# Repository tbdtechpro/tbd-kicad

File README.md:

# tbd-kicad

KiCad 9 symbols, footprints and 3D models for hobby-electronics modules that are awkward to find ready-made:
development boards, display modules, audio DACs, level-shifter breakouts, an encoder module, optocouplers, solderable
breadboard and proto boards, a 3.5 mm jack and a MIDI shield. Each part is complete: a symbol with sensible pin types, a footprint
with the real hole pattern, a 3D body for the viewer, and a note on where every dimension came from.

Everything here is generated from Python scripts, so a measurement fix rebuilds the whole library consistently. Use
it under CC-BY-SA 4.0 with the KiCad library exception: designs made with it are yours, no attribution needed on boards.

## Parts

| Part | Symbol | Footprint | 3D | Geometry source |
|---|---|---|---|---|
| **Development boards** | | | | |
| PJRC Teensy 4.1 | `Teensy_4.1` | `Teensy41` | STEP + coloured VRML | XenGi library (exact) |
| Espressif ESP32-S3-DevKitC-1 (and N16R8 clones) | `ESP32-S3-DevKitC-1` | `ESP32-S3-DevKitC-1` | VRML + STEP | Espressif library (exact) |
| DFRobot Beetle RP2350 (DFR1188) | `Beetle_RP2350_DFR1188` | `Beetle_RP2350_DFR1188_THT`, `_SMD` | VRML + STEP (THT) | DFRobot CAD (exact) |
| Waveshare RP2040-Zero form factor | `RP2040-Zero` | `RP2040-Zero` | VRML + STEP | Waveshare drawing (edge pins exact, back pads approx.) |
| Waveshare RP2350B-Plus-W (Pico 2 W form factor, RP2350B) | `RP2350B-Plus-W` | `RP2350B-Plus-W` | VRML + STEP | Waveshare drawing + board (pins exact, back pads +/-0.3 mm) |
| **Displays** | | | | |
| 2.8" ILI9341 SPI TFT, 14-pin (lcdwiki MSP2806/MSP2807) | `TFT_2.8in_ILI9341_SPI_MSP2806` | same | VRML + STEP | lcdwiki drawing (exact) |
| 1.5" SH1107 128x128 OLED, I2C 4-pin (HiLetgo / GME128128-01-IIC) | `OLED_1.5in_SH1107_128x128_I2C` | same | VRML + STEP | calipers (PCB, holes, header, glass) |
| 1.28" round GC9A01 IPS, 7-pin | `GC9A01_Round_1.28in_7pin` | same | VRML + STEP | header exact, outline from photos |
| **Audio** | | | | |
| Adafruit PCM5102 / PCM5100 I2S DAC (6250 / 6251) | `Adafruit_PCM510x_I2S_DAC` | same | VRML + STEP | Adafruit EagleCAD (exact) |
| Lonely Binary TK103 PCM5102A I2S DAC (right-angle header) | `TK103_PCM5102A_I2S_DAC` | `TK103_Module_RA_Header` | vendor STEP, see note | vendor STEP (exact) |
| Kycon STX-3120-3B 3.5 mm stereo jack (Adafruit 1699) | `AudioJack_3.5mm_STX-3120-3B` | `Jack_3.5mm_Kycon_STX-3120-3B_Horizontal` | VRML + STEP | Kycon drawing (exact) |
| Arduino UNO MIDI shield (3x DIN-5, 6N138, marking K194725ASJH) | `MIDI_Shield_DIN5x3_6N138` | `MIDI_Shield_K194725ASJH` | VRML + STEP (from `projects/midi-shield`) | UNO 6+6/8+8 header pattern (exact), parts from photos and calipers |
| **Breakouts and modules** | | | | |
| Adafruit TXB0104 bi-directional level shifter (1875) | `Adafruit_TXB0104_Level_Shifter` | `Adafruit_TXB0104_Breakout` | VRML + STEP | Adafruit EagleCAD (exact) |
| Adafruit BSS138 4-channel I2C-safe level shifter (757) | `Adafruit_BSS138_4ch_Level_Shifter` | `Adafruit_BSS138_Level_Shifter` | VRML + STEP | Adafruit EagleCAD (exact) |
| KY-040 rotary encoder module (right-angle header) | `KY-040_Rotary_Encoder_Module` | `KY-040_Module_RA_Header` | VRML + STEP | header exact, board from photos |
| ProtoSupplies 3.5 mm TRRS jack breakout | `TRRS_3.5mm_Jack_Breakout` | same | VRML + STEP | listing size, photos |
| ProtoSupplies WS2812 RGB LED module | `WS2812_RGB_LED_Module` | same | VRML + STEP | listing size, photos |
| ProtoSupplies MicroSD card module (3.3 V, SPI) | `MicroSD_Card_Module_SPI_3V3` | same | VRML + STEP | listing size, photos |
| Teansic USB-C female breakout, 16-pin receptacle, 6-pin header | `USB-C_Breakout_16P_6pin` | same | VRML + STEP | listing size, photos |
| **Connectors and switches** | | | | |
| DIN-5 180° PCB socket (as on the MIDI shield) | stock `Connector:DIN-5_180degree` | `DIN-5_180deg_PCB_Socket` | VRML + STEP (converted CAD model) | pin spacing by calipers, lugs from photos |
| SPDT slide switch, 2.5 mm pitch with lugs (as on the MIDI shield) | stock `Switch:SW_SPDT` | `SW_Slide_SPDT_P2.5mm_Lugs` | VRML + STEP | pitch and lugs from photos |
| Miniature 6 x 6 mm tactile pushbutton, 2 leads on 5.08 mm (ProtoSupplies 10-pack) | stock `Switch:SW_Push` | `SW_Push_6x6mm_2pin_P5.08mm` | VRML + STEP | listing dimensions |
| **Optocouplers** | | | | |
| Sharp PC900V OPIC photocoupler (MIDI in) | `PC900V` | stock `Package_DIP:DIP-6_W7.62mm` | stock | Sharp drawing (exact) |
| Toshiba TLP2962 15 MBd photocoupler | `TLP2962` | stock `Package_DIP:DIP-8_W7.62mm` | stock | Toshiba drawing (exact) |
| **Covered by stock KiCad** | | | | |
| APMemory APS6404L / ESP-PSRAM64H 8 MB QSPI PSRAM (Teensy 4.1 add-on) | stock `Memory_RAM:APS6404L-SQRx-SN` | stock `Package_SO:SOIC-8_3.9x4.9mm_P1.27mm` | stock | datasheet (SOP-8 150 mil) |
| **Prototyping boards** | | | | |
| ElectroCookie full-size solderable breadboard PCB | (mechanical) | `ElectroCookie_Breadboard_Full` | | vendor drawing (exact), rails from photos |
| ProtoSupplies PSB-1 MCU proto board with DC input | (mechanical) | `ProtoSupplies_PSB-1`, `ProtoSupplies_PSB-1_DCKit` | board STEP (bare / with kit); the DCKit carrier shows the kit parts | vendor drawing, CAD renders, the board itself |
| PSB-1 pieces used to redraw the board | | `ProtoSupplies_PSB-1_Grid`, `PSB-1_Header_2x20_Breakout`, `PSB-1_Header_2x10_Staggered_Breakout` | | same |
| M3 hex standoff, 6 mm (mechanical, used in the parts preview) | (mechanical) | `Standoff_M3_H6mm` | VRML + STEP | nominal |

Also included: silkscreen logo footprints in two sizes each (`Logo_TBD_*`, `Logo_Star_*`), filled polygons on F.SilkS
with no pads, made by `tools/gen_logos.py` from a PNG. Point the script at your own artwork to make more.

`docs/components.md` describes each part, lists the source of every dimension, and flags what is still only estimated.

## Installing

Requires KiCad 9.0 (the files use the 9.0 formats).

1. Clone or download this repository somewhere permanent, for example `~/kicad/tbd-kicad`.
2. In KiCad, open *Preferences > Configure Paths* and add a variable `TBD_KICAD_DIR` whose value is that directory.
   The footprints reference their 3D models as `${TBD_KICAD_DIR}/lib/3d/...`, so without it the models do not show.
3. *Preferences > Manage Symbol Libraries*, Global tab: add `${TBD_KICAD_DIR}/lib/tbd.kicad_sym` with nickname `tbd`.
4. *Preferences > Manage Footprint Libraries*, Global tab: add `${TBD_KICAD_DIR}/lib/tbd.pretty` with nickname `tbd`.

Keep the nickname `tbd`: every symbol's Footprint field is pre-filled as `tbd:<footprint>`, so placing a symbol gives you
the footprint and 3D model with no further assignment. To use the library in a single project instead of globally,
copy `projects/teensy-panel/sym-lib-table` and `fp-lib-table` next to your project file and edit the paths.

Not using a path variable? Add the libraries by absolute path and run a find-and-replace of `${TBD_KICAD_DIR}` in
`lib/tbd.pretty/*.kicad_mod`; nothing else in the repository depends on it.

## Conventions

- **Pin numbers follow the module's silkscreen or vendor drawing**, counted the way you would read the board (the
  Teensy and ESP32 symbols keep their upstream numbering). Pin names are the names printed on the module.
- **Modules with right-angle headers** (KY-040, TK103) have a *carrier* footprint: a 1xN row of holes with the module
  standing perpendicular on the -Y side. The 3D model shows the module standing.
- **Modules with straight headers** are modelled sitting on soldered male headers, board 2.54 mm above the carrier.
- **Prototyping boards** name their pads after the net they belong to (`L12` for strip holes A-E of row 12 on the
  ElectroCookie, `G`, `V1`-`V7`, `VIN`, `a7` on the PSB-1), so every hole of a strip or rail carries the same pad
  number. The copper lines in those footprints are decoration for the 3D view; KiCad 9 does not treat same-numbered
  pads as connected, so add board-level tracks along the strips if you want the ratsnest to understand the board
  (`projects/teensy-panel` shows how).
- **Mounting holes** are non-plated unless the vendor board plates them (Adafruit's are plated).
- **Logo footprints** are board-only, excluded from the BOM and position files; flip them for the back side.

## How accurate is it

Exact means the geometry comes from vendor CAD, a dimensioned drawing or a STEP file; those parts are safe to drill from.
Items measured from photos (GC9A01 outline and holes, KY-040 board size, RP2040-Zero back pads, ElectroCookie rail
length, the PSB-1 input-section component positions) are close but should be checked with calipers before a panel is
cut. The PSB-1 footprints keep the seven V bus columns as separate nets because the vendor renders show them as
separate copper; measure your board and set `V_COMMON = True` in `tools/psb1_geometry.py` if they are joined.

If you find an error, open an issue with a measurement or a drawing and it gets fixed in the generator.

## Example projects

- **`projects/teensy-panel`**: a Teensy 4.1 front panel (round display, encoder, I2S DAC) built on the ElectroCookie
  board. The PCB is a build guide rather than a fab file: sockets, modules and every jumper wire routed hole-to-hole and
  rendered as 22 AWG wire in the 3D viewer, with a wiring map (`WIRING.md`) and cut list (`WIRES.md`).
- **`projects/parts-preview`**: the board in the picture above, every other part placed for a look in the 3D viewer;
  the PSB-1 sits on 6 mm standoffs as a separate board with the small breakouts plugged into it.
- **`projects/midi-shield`**: the K194725ASJH Arduino MIDI shield redrawn: schematic (6N138 input, TX output, THRU,
  upload switch, reset, D2-D13 and A0-A5 broken out to the proto rows), a routed two-layer layout in the true top-view frame, and the source of the
  `MIDI_Shield_K194725ASJH` footprint and `lib/3d/MIDI_Shield_K194725ASJH.step`. Also adds the DIN-5 socket and
  slide switch footprints it is built from.
- **`projects/psb-1`**: the ProtoSupplies PSB-1 itself redrawn in KiCad: schematic of the DC-input section and headers,
  the full layout with every bus, strip and breakout trace, and two board files, `psb-1.kicad_pcb` with the component
  kit fitted and `psb-1-bare.kicad_pcb` as sold. `lib/3d/ProtoSupplies_PSB-1*.step` are exported from them.

## Layout and regenerating

```
lib/tbd.kicad_sym         all symbols                   <- tools/gen_lib.py
lib/tbd.pretty/           all footprints                <- tools/gen_lib.py, tools/gen_logos.py
lib/3d/                   VRML + STEP bodies            <- tools/build_models.py (FreeCAD); Teensy STEP from XenGi
lib/vendor/               upstream files the generator reads, with their licences
artwork/                  logo sources and logos.json
docs/components.md        part reference and dimension sources
projects/                 example projects              <- tools/gen_teensy_panel.py, gen_parts_preview.py, gen_psb1.py
tools/                    the generators (Python 3, KiCad's pcbnew module for the projects, FreeCAD for the models)
```

```
python3 tools/gen_lib.py                        # symbols and footprints
freecad.cmd tools/build_models.py               # 3D bodies (run from a path FreeCAD can read; snap builds cannot see /tmp)
python3 tools/gen_logos.py artwork/logos.json   # logo footprints (needs potrace)
python3 tools/gen_teensy_panel.py               # projects/teensy-panel
python3 tools/gen_parts_preview.py              # projects/parts-preview
python3 tools/gen_psb1.py                       # projects/psb-1 (geometry shared with gen_lib.py in tools/psb1_geometry.py)
python3 -I tools/eagle_dump.py <board.brd>      # pads, outline and nets of an EagleCAD board, for new parts
```

Adding a part means adding a block to `gen_lib.py` (symbol pin list, pad coordinates, outline) and, if you want a body,
a builder in `build_models.py`. Checks used before committing: `kicad-cli sym export svg`, `kicad-cli fp export svg`,
`kicad-cli sch erc` on the example schematic and `kicad-cli pcb render` on the example boards.

## Vendor files

Redistributable upstream sources live in `lib/vendor/`: XenGi's Teensy library (MIT), Espressif's KiCad library
(CC-BY-SA 4.0, converted from the KiCad 10 format) and Adafruit's EagleCAD boards (CC-BY-SA 3.0). Vendor documents
without redistribution terms (DFRobot CAD, lcdwiki and Kycon drawings, the Lonely Binary STEP, ProtoSupplies renders)
stay in a private companion repository; the only visible effect is that the TK103 footprint's 3D model is absent here.

## Licence

Library content CC-BY-SA 4.0 with the KiCad library exception, tools MIT, vendored items under their own terms.
See `LICENSE.md`.

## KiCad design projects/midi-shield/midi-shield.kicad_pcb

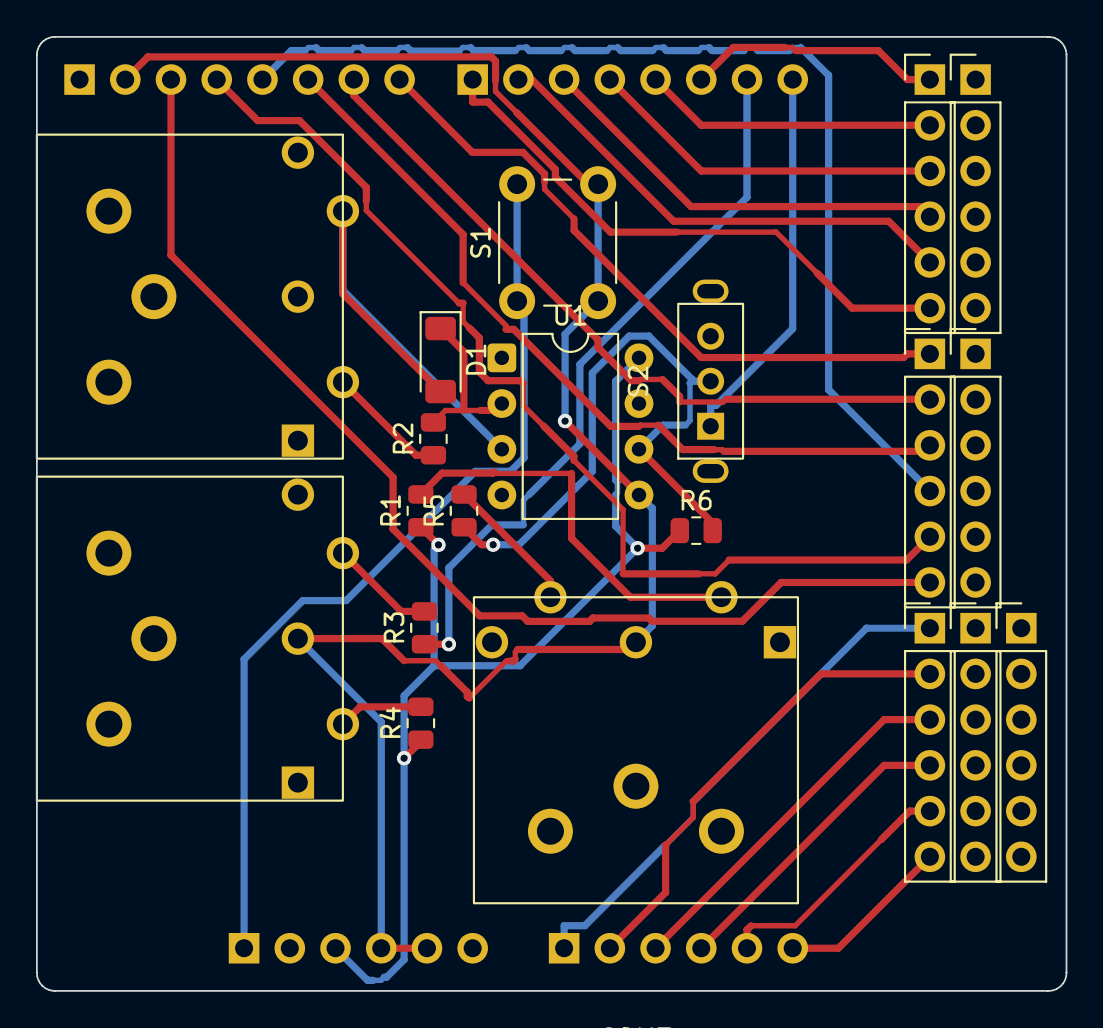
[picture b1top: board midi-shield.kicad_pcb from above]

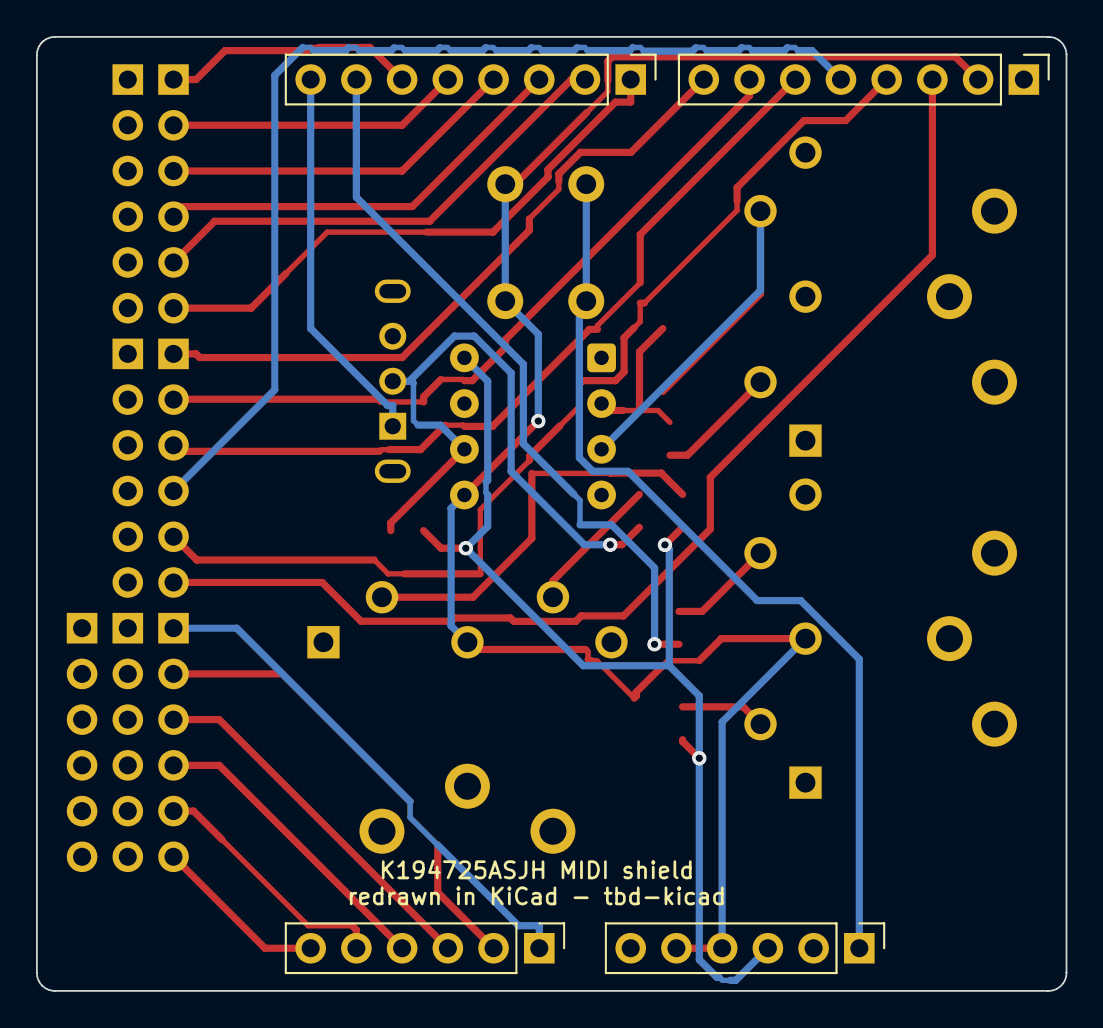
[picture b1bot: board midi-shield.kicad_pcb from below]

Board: 2 copper layers, 57.2 x 53.0 mm, 24 parts (4 on the bottom side), 31 nets.

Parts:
COM1: MIDI IN; DIN-5_180deg_PCB_Socket
COM2: MIDI OUT; DIN-5_180deg_PCB_Socket
COM3: MIDI THRU; DIN-5_180deg_PCB_Socket
D1: 1N4148; D_MiniMELF
J1: UNO RESET..VIN; PinHeader_1x06_P2.54mm_Vertical
J2: UNO A0..A5; PinHeader_1x06_P2.54mm_Vertical
J3: UNO AREF..D8; PinHeader_1x08_P2.54mm_Vertical
J4: UNO D7..RX; PinHeader_1x08_P2.54mm_Vertical
P4, P5, P6, P7, P8, P9, P10: proto; PinHeader_1x06_P2.54mm_Vertical
R1, R2, R3, R4, R5, R6: 220; R_0805_2012Metric
S1: RESET; SW_PUSH_6mm
S2: RX ON/OFF; SW_Slide_SPDT_P2.5mm_Lugs
U1: 6N138; DIP-8_W7.62mm

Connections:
+5V: J1.3, R1.1, R4.1, R6.1, U1.8
A0: J2.1, P6.1
A1: J2.2, P6.2
A2: J2.3, P6.3
A3: J2.4, P6.4
A4: J2.5, P6.5
A5: J2.6, P6.6
D2: J4.6, P4.1
D3: J4.5, P4.2
D4: J4.4, P4.3
D5: J4.3, P4.4
D6: J4.2, P4.5
D7: J4.1, P4.6
D8: J3.8, P5.1
D9: J3.7, P5.2
D10: J3.6, P5.3
D11: J3.5, P5.4
D12: J3.4, P5.5
D13: J3.3, P5.6
GND: COM2.2, COM3.2, J1.4, J1.5, J3.2, S1.2, U1.5
IN_4: COM1.4, R2.1
IN_A: D1.1, R2.2, U1.2
IN_K: COM1.5, D1.2, U1.3
OPTO_OUT: R5.1, R6.2, S2.2, U1.6
OUT_4: COM2.4, R4.2
OUT_5: COM2.5, R3.2
RESET: J1.1, S1.1
RX: J4.8, S2.1
THRU_4: COM3.4, R1.2
THRU_5: COM3.5, R5.2
TX: J4.7, R3.1

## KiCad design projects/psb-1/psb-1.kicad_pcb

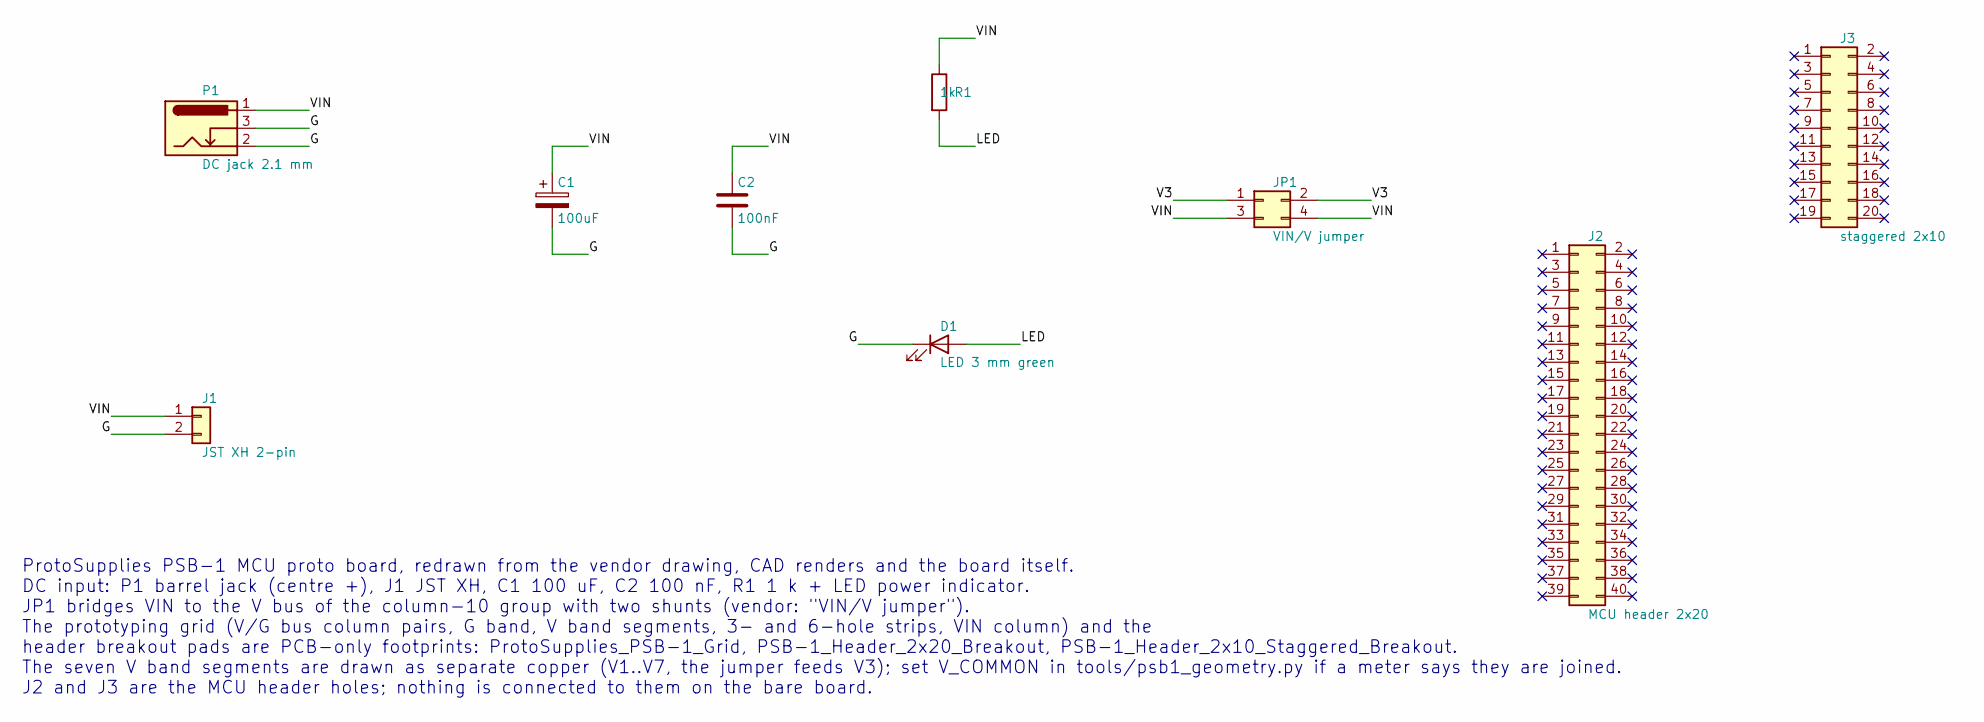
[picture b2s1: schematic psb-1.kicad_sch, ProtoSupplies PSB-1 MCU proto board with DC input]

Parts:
C1: 100uF; CP_Radial_D5.0mm_P2.00mm
C2: 100nF; C_Disc_D5.0mm_W2.5mm_P2.50mm
D1: LED 3 mm green; LED_D3.0mm
J1: JST XH 2-pin; JST_XH_B2B-XH-A_1x02_P2.50mm_Vertical
J2: MCU header 2x20; PSB-1_Header_2x20_Breakout
J3: staggered 2x10; PSB-1_Header_2x10_Staggered_Breakout
JP1: VIN/V jumper; PinHeader_2x02_P2.54mm_Vertical
P1: DC jack 2.1 mm; BarrelJack_GCT_DCJ200-10-A_Horizontal
R1: 1k; R_Axial_DIN0207_L6.3mm_D2.5mm_P10.16mm_Horizontal

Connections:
G: C1.2, C2.2, D1.1 (K), J1.2, P1.2, P1.3; also elsewhere on the board
H1: J2.1
H2: J2.2
H3: J2.3
H4: J2.4
H5: J2.5
H6: J2.6
H7: J2.7
H8: J2.8
H9: J2.9
H10: J2.10
H11: J2.11
H12: J2.12
H13: J2.13
H14: J2.14
H15: J2.15
H16: J2.16
H17: J2.17
H18: J2.18
H19: J2.19
H20: J2.20
H21: J2.21
H22: J2.22
H23: J2.23
H24: J2.24
H25: J2.25
H26: J2.26
H27: J2.27
H28: J2.28
H29: J2.29
H30: J2.30
H31: J2.31
H32: J2.32
H33: J2.33
H34: J2.34
H35: J2.35
H36: J2.36
H37: J2.37
H38: J2.38
H39: J2.39
H40: J2.40
K1: J3.1
K2: J3.2
K3: J3.3
K4: J3.4
K5: J3.5
K6: J3.6
K7: J3.7
K8: J3.8
K9: J3.9
K10: J3.10
K11: J3.11
K12: J3.12
K13: J3.13
K14: J3.14
K15: J3.15
K16: J3.16
K17: J3.17
K18: J3.18
K19: J3.19
K20: J3.20
LED: D1.2 (A), R1.2
V3: JP1.1, JP1.2; also elsewhere on the board
VIN: C1.1, C2.1, J1.1, JP1.3, JP1.4, P1.1, R1.1; also elsewhere on the board

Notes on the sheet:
ProtoSupplies PSB-1 MCU proto board, redrawn from the vendor drawing, CAD renders and the board itself. DC input: P1 barrel jack (centre +), J1 JST XH, C1 100 uF, C2 100 nF, R1 1 k + LED power indicator. JP1 bridges VIN to the V bus of the column-10 group with two shunts (vendor: "VIN/V jumper"). T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

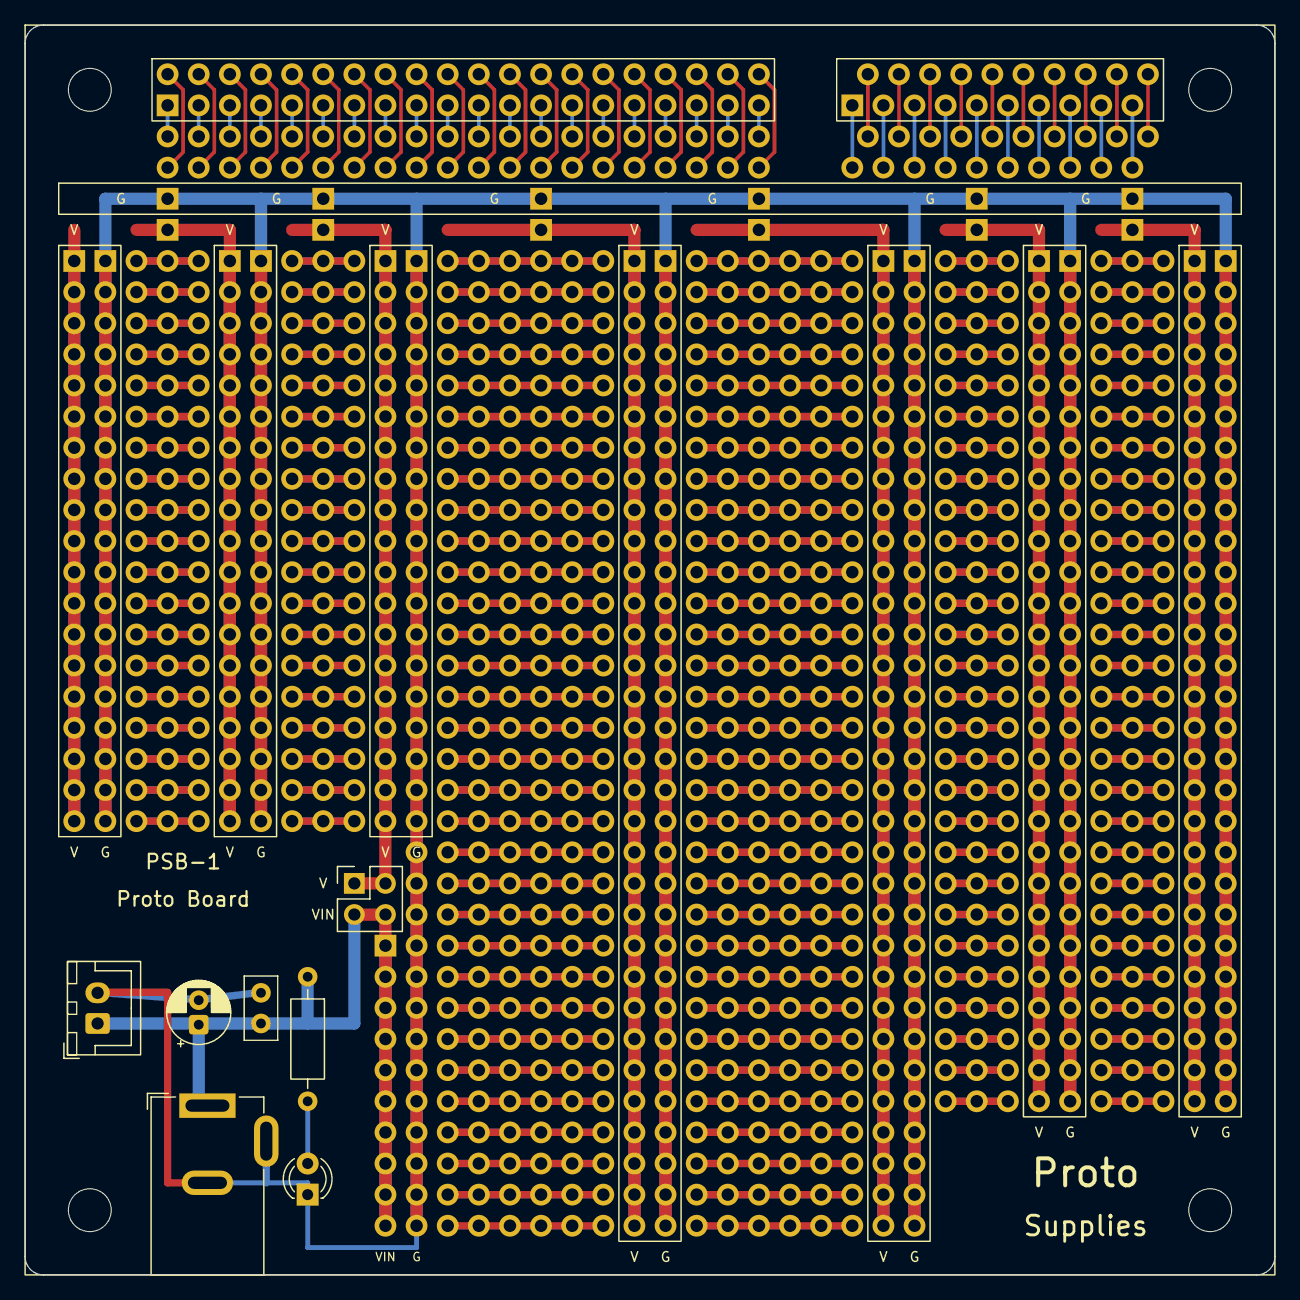
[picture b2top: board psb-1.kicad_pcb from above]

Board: 2 copper layers, 102.0 x 102.0 mm, 10 parts (0 on the bottom side), 4 nets.

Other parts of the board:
PB1: PSB-1 grid; ProtoSupplies_PSB-1_Grid

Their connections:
G: PB1.G; also elsewhere on the board
V3: PB1.V3; also elsewhere on the board
VIN: PB1.VIN; also elsewhere on the board

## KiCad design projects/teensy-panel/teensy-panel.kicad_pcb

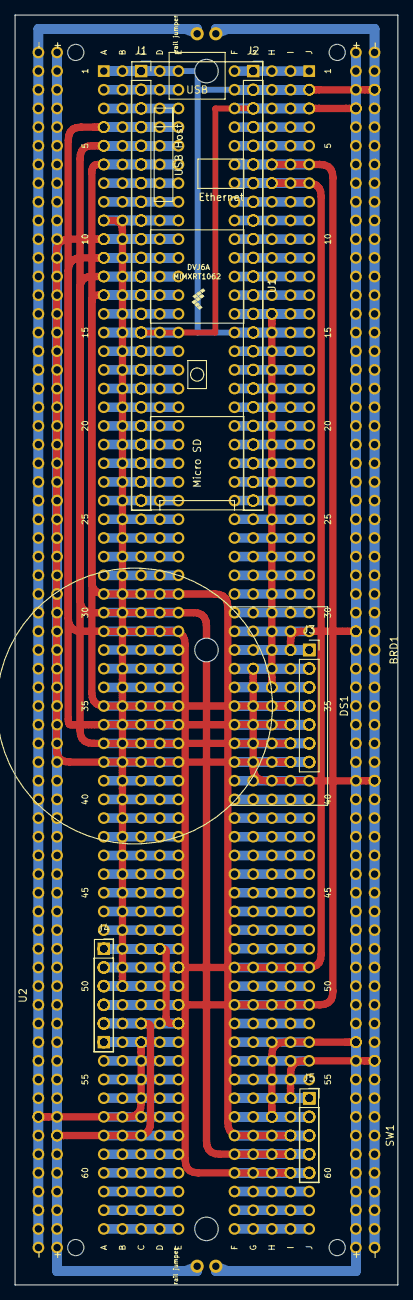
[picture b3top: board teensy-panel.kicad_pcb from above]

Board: 2 copper layers, 52.1 x 172.7 mm, 30 parts (0 on the bottom side), 13 nets.

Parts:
BRD1: ElectroCookie_Breadboard_Full
DS1: GC9A01_Round_1.28in_7pin
J1, J2: PinSocket_1x24; PinSocket_1x24_P2.54mm_Vertical
J3: PinSocket_1x07; PinSocket_1x07_P2.54mm_Vertical
J4: PinSocket_1x06; PinSocket_1x06_P2.54mm_Vertical
J5: PinSocket_1x05; PinSocket_1x05_P2.54mm_Vertical
SW1: KY-040_Rotary_Encoder_Module; KY-040_Module_RA_Header
U1: Teensy_4.1; Teensy41
U2: TK103_PCM5102A_I2S_DAC; TK103_Module_RA_Header
W01, W03, W16, W18, W19: +3V3; JumperWire
W02, W04, W17, W20: GND; JumperWire
W05: SPI_SCK; JumperWire
W06: SPI_MOSI; JumperWire
W07: LCD_DC; JumperWire
W08: LCD_CS; JumperWire
W09: LCD_RST; JumperWire
W10: ENC_SW; JumperWire
W11: ENC_DT; JumperWire
W12: ENC_CLK; JumperWire
W13: I2S_DIN; JumperWire
W14: I2S_LRCK; JumperWire
W15: I2S_BCK; JumperWire

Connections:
+3V3: BRD1.B+, BRD1.L15, BRD1.R3, BRD1.T+, DS1.1, J1.15, J2.3, J3.1, J4.1, J4.5, J5.2, SW1.2, U1.15, U1.46, U2.2, U2.6, W01.1, W01.2, W03.1, W03.2, W16.1, W16.2, W18.1, W18.2, W19.1, W19.2
ENC_CLK: BRD1.L4, J1.4, J5.5, SW1.5, U1.4, W12.1, W12.2
ENC_DT: BRD1.L5, J1.5, J5.4, SW1.4, U1.5, W11.1, W11.2
ENC_SW: BRD1.L6, J1.6, J5.3, SW1.3, U1.6, W10.1, W10.2
GND: BRD1.B-, BRD1.L1, BRD1.R2, BRD1.R15, BRD1.T-, DS1.2, J1.1, J2.2, J2.15, J3.2, J4.6, J5.1, SW1.1, U1.1, U1.34, U1.47, U2.1, W02.1, W02.2, W04.1, W04.2, W17.1, W17.2, W20.1, W20.2
I2S_BCK: BRD1.R6, J2.6, J4.4, U1.43, U2.3, W15.1, W15.2
I2S_DIN: BRD1.L9, J1.9, J4.3, U1.9, U2.4, W13.1, W13.2
I2S_LRCK: BRD1.R7, J2.7, J4.2, U1.42, U2.5, W14.1, W14.2
LCD_CS: BRD1.L12, DS1.6, J1.12, J3.6, U1.12, W08.1, W08.2
LCD_DC: BRD1.L11, DS1.5, J1.11, J3.5, U1.11, W07.1, W07.2
LCD_RST: BRD1.L10, DS1.7, J1.10, J3.7, U1.10, W09.1, W09.2
SPI_MOSI: BRD1.L13, DS1.4, J1.13, J3.4, U1.13, W06.1, W06.2
SPI_SCK: BRD1.R14, DS1.3, J2.14, J3.3, U1.35, W05.1, W05.2

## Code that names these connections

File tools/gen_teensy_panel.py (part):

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# xtragravy/bench/teensy41/README.md: display SCL/SDA = 13/11, CS/DC/RST = 10/9/8, encoder CLK/DT/SW = 2/3/4,
# DAC BCK/LRCK/DIN = 21/20/7.
TEENSY_NETS = {
    '4': 'ENC_CLK', '5': 'ENC_DT', '6': 'ENC_SW',          # GPIO 2, 3, 4
    '9': 'I2S_DIN',                                        # GPIO 7 (OUT1A)
    '10': 'LCD_RST', '11': 'LCD_DC', '12': 'LCD_CS',       # GPIO 8, 9, 10
    '13': 'SPI_MOSI', '35': 'SPI_SCK',                     # GPIO 11, 13
    '42': 'I2S_LRCK', '43': 'I2S_BCK',                     # GPIO 20, 21
    '15': '+3V3', '46': '+3V3', '1': 'GND', '34': 'GND', '47': 'GND',
}
MODULES = {
    # ref: (symbol, {pin: net}, sheet position)
    'DS1': ('GC9A01_Round_1.28in_7pin', {'1': '+3V3', '2': 'GND', '3': 'SPI_SCK', '4': 'SPI_MOSI', '5': 'LCD_DC',
                                         '6': 'LCD_CS', '7': 'LCD_RST'}, (254.0, 101.6)),
    'SW1': ('KY-040_Rotary_Encoder_Module', {'1': 'GND', '2': '+3V3', '3': 'ENC_SW', '4': 'ENC_DT', '5': 'ENC_CLK'},
            (55.88, 114.3)),
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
